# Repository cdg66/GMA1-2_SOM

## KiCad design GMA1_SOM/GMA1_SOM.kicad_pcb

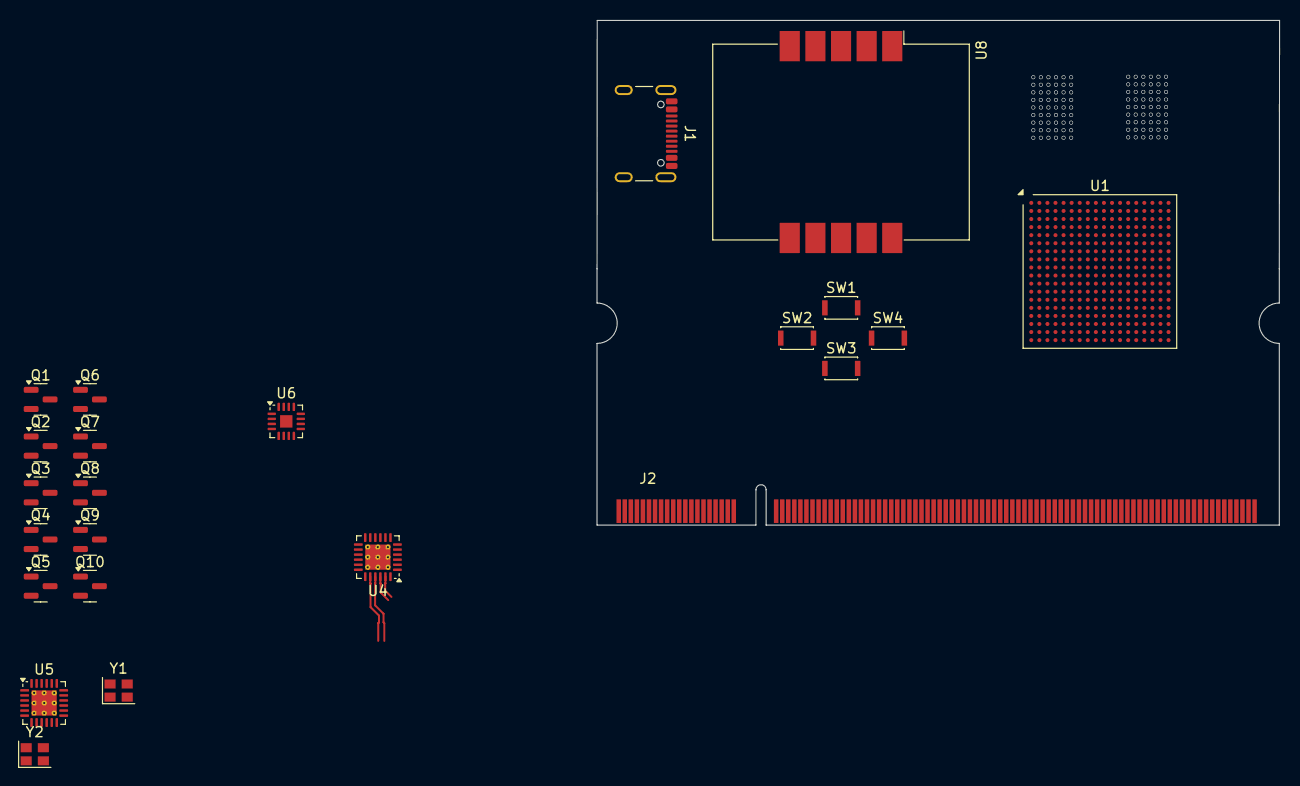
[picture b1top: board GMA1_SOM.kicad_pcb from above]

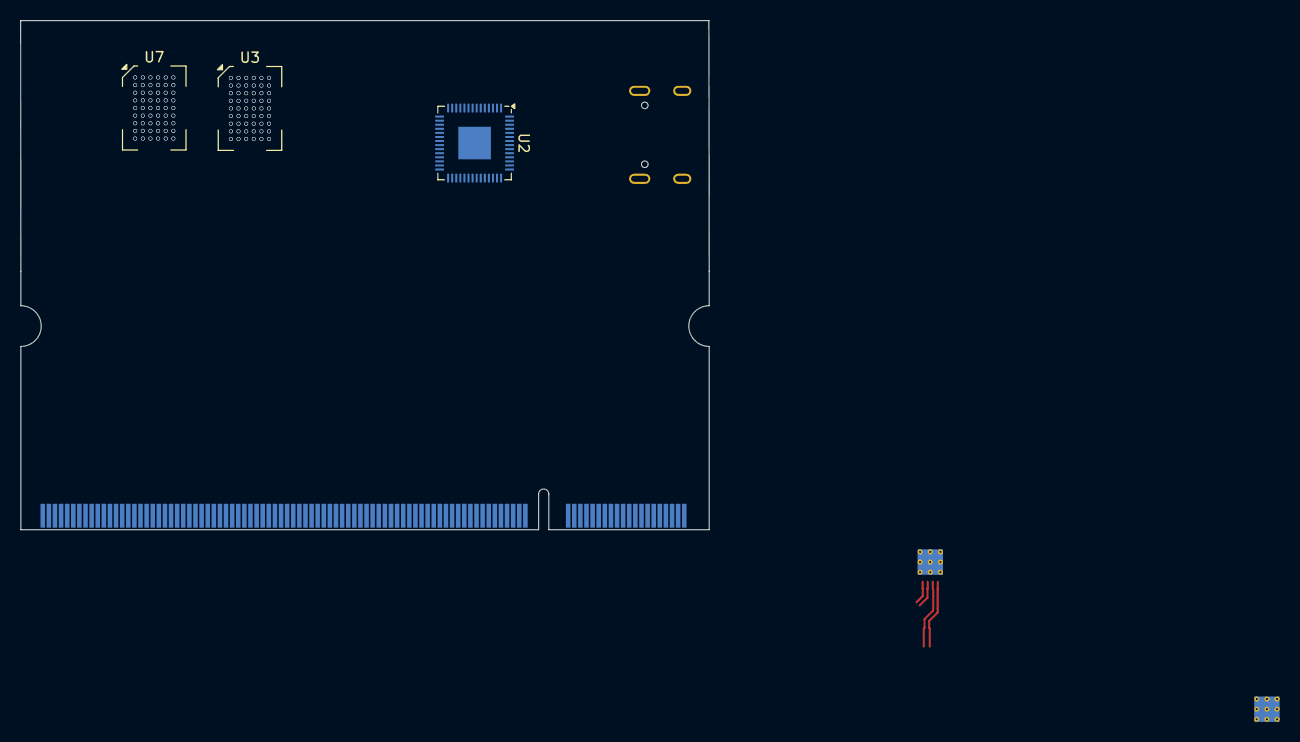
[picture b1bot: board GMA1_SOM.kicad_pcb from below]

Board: 6 copper layers, 67.6 x 50.0 mm, 26 parts (3 on the bottom side), 90 nets.

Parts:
J1: USB4105-GF-A; USB_C_Receptacle_GCT_USB4105-xx-A_16P_TopMnt_Horizontal
J2: SODIMM-200_Split; SODIMM-200_1.8V_Card_edge
Q1, Q2, Q3, Q4, Q5, Q6, Q7, Q8, Q9, Q10: BSS138; SOT-23
SW1, SW2, SW3, SW4: KXT 331 LHS; SW_SPST_CK_KXT3
U1: CCGM1A1; BGA-324_15.0x15.0mm_Layout18x18_P0.8mm_Ball0.45mm_Pad0.4mm_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
U2: RP2040; QFN-56-1EP_7x7mm_P0.4mm_EP3.2x3.2mm
U3, U7: IS66WVC2M16EALL-7010BLI; BGA-54_6x9_6.0x8.0mm
U4, U5: LAN8742A-CZ-TR; VQFN-24-1EP_4x4mm_P0.5mm_EP2.5x2.5mm_ThermalVias
U6: MAX98357B; TQFN-16-1EP_3x3mm_P0.5mm_EP1.23x1.23mm
U8: HDSM-543B; HDSM-541B_HDSM-543B
Y1, Y2: SG-210STF 25.0000ML0; Oscillator_SMD_SeikoEpson_SG210-4Pin_2.5x2.0mm

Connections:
+1V2: U4.6 (VDDCR), U5.6 (VDDCR)
+1V8: U3.D6 (VDD), U3.E1 (VDDQ), U4.9 (VDDIO), U5.9 (VDDIO), U7.D6 (VDD), U7.E1 (VDDQ), Y1.1 (~ST), Y1.4 (Vcc), Y2.1 (~ST), Y2.4 (Vcc)
+3V3A: U4.1 (VDD2A), U4.19 (VDD1A), U5.1 (VDD2A), U5.19 (VDD1A)
/Root/ETHERNET1/RXN: J2.187, U5.22 (RXN)
/Root/ETHERNET1/RXP: J2.189, U5.23 (RXP)
/Root/ETHERNET1/TXN: J2.181, U5.20 (TXN)
/Root/ETHERNET1/TXP: J2.183, U5.21 (TXP)
/Root/ETHERNET/RXN: J2.167, U4.22 (RXN)
/Root/ETHERNET/RXP: J2.169, U4.23 (RXP)
/Root/ETHERNET/TXN: J2.161, U4.20 (TXN)
/Root/ETHERNET/TXP: J2.163, U4.21 (TXP)
/Root/ETHERNET/~INT/REFCLKO: U1.N14 (CLK0/IO_SB_A8), U4.14 (~INT/REFCLKO)
/Root/FPGA/A0: U1.B9 (IO_NB_A0), U3.A3 (A0), U7.A3 (A0)
/Root/FPGA/A1: U1.A9 (IO_NB_B0), U3.A4 (A1), U7.A4 (A1)
/Root/FPGA/A2: U1.D10 (IO_NB_A1), U3.A5 (A2), U7.A5 (A2)
/Root/FPGA/A3: U1.C10 (IO_NB_B1), U3.B3 (A3), U7.B3 (A3)
/Root/FPGA/A4: U1.B11 (IO_NB_A2), U3.B4 (A4), U7.B4 (A4)
/Root/FPGA/A5: U1.A11 (IO_NB_B2), U3.C3 (A5), U7.C3 (A5)
/Root/FPGA/A6: U1.D11 (IO_NB_A3), U3.C4 (A6), U7.C4 (A6)
/Root/FPGA/A7: U1.C11 (IO_NB_B3), U3.D4 (A7), U7.D4 (A7)
/Root/FPGA/A8: U1.B12 (IO_NB_A4), U3.H2 (A8), U7.H2 (A8)
/Root/FPGA/A9: U1.A12 (IO_NB_B4), U3.H3 (A9), U7.H3 (A9)
/Root/FPGA/A10: U1.D12 (IO_NB_A5), U3.H4 (A10), U7.H4 (A10)
/Root/FPGA/A11: U1.C12 (IO_NB_B5), U3.H5 (A11), U7.H5 (A11)
/Root/FPGA/A12: U1.D13 (IO_NB_A6), U3.G3 (A12), U7.G3 (A12)
/Root/FPGA/A13: U1.C13 (IO_NB_B6), U3.G4 (A13), U7.G4 (A13)
/Root/FPGA/A14: U1.B14 (IO_NB_A7), U3.F3 (A14), U7.F3 (A14)
/Root/FPGA/A15: U1.A14 (IO_NB_B7), U3.F4 (A15), U7.F4 (A15)
/Root/FPGA/A16: U1.D14 (IO_NB_A8), U3.E4 (A16), U7.E4 (A16)
/Root/FPGA/A17: U1.C14 (IO_NB_B8), U3.D3 (A17), U7.D3 (A17)
/Root/FPGA/A18: U1.D9 (IO_NA_B8), U3.H1 (A18), U7.H1 (A18)
/Root/FPGA/A19: U1.C9 (IO_NA_A8), U3.G2 (A19), U7.G2 (A19)
/Root/FPGA/A20: U1.B8 (IO_NA_B7), U3.H6 (A20), U7.H6 (A20)
/Root/FPGA/CLK: U1.G16 (IO_EA_A8), U3.J2 (CLK), U7.J2 (CLK)
/Root/FPGA/CRE: U1.J16 (IO_EA_A5), U3.A6 (CRE), U7.A6 (CRE)
/Root/FPGA/DQ0: U1.G15 (IO_EA_B8), U3.B6 (DQ0), U7.B6 (DQ0)
/Root/FPGA/DQ1: U1.A3 (IO_NA_A0), U3.C5 (DQ1), U7.C5 (DQ1)
/Root/FPGA/DQ2: U1.B3 (IO_NA_B0), U3.C6 (DQ2), U7.C6 (DQ2)
/Root/FPGA/DQ3: U1.A4 (IO_NA_A1), U3.D5 (DQ3), U7.D5 (DQ3)
/Root/FPGA/DQ4: U1.B4 (IO_NA_B1), U3.E5 (DQ4), U7.E5 (DQ4)
/Root/FPGA/DQ5: U1.B5 (IO_NA_A2), U3.F5 (DQ5), U7.F5 (DQ5)
/Root/FPGA/DQ6: U1.C5 (IO_NA_B2), U3.F6 (DQ6), U7.F6 (DQ6)
/Root/FPGA/DQ7: U1.C6 (IO_NA_A3), U3.G6 (DQ7), U7.G6 (DQ7)
/Root/FPGA/DQ8: U1.D6 (IO_NA_B3), U3.B1 (DQ8), U7.B1 (DQ8)
/Root/FPGA/DQ9: U1.A6 (IO_NA_A4), U3.C1 (DQ9), U7.C1 (DQ9)
/Root/FPGA/DQ10: U1.B6 (IO_NA_B4), U3.C2 (DQ10), U7.C2 (DQ10)
/Root/FPGA/DQ11: U1.C7 (IO_NA_A5), U3.D2 (DQ11), U7.D2 (DQ11)
/Root/FPGA/DQ12: U1.D7 (IO_NA_B5), U3.E2 (DQ12), U7.E2 (DQ12)
/Root/FPGA/DQ13: U1.C8 (IO_NA_A6), U3.F2 (DQ13), U7.F2 (DQ13)
/Root/FPGA/DQ14: U1.D8 (IO_NA_B6), U3.F1 (DQ14), U7.F1 (DQ14)
/Root/FPGA/DQ15: U1.A8 (IO_NA_A7), U3.G1 (DQ15), U7.G1 (DQ15)
/Root/FPGA/IO_WB_A2: SW4.2, U1.L3 (IO_WB_A2)
/Root/FPGA/IO_WB_A3: SW1.2, U1.L1 (IO_WB_A3)
/Root/FPGA/IO_WB_B2: SW3.2, U1.L4 (IO_WB_B2)
/Root/FPGA/IO_WB_B3: SW2.2, U1.L2 (IO_WB_B3)
/Root/FPGA/WAIT0: U1.J18 (IO_EA_A4), U3.J1 (WAIT)
/Root/FPGA/WAIT1: U1.K15 (IO_EA_B3), U7.J1 (WAIT)
/Root/FPGA/~ADV: U1.G17 (IO_EA_B7), U3.J3 (~ADV), U7.J3 (~ADV)
/Root/FPGA/~CE: U1.H15 (IO_EA_B6), U3.B5 (~CE), U7.B5 (~CE)
/Root/FPGA/~LB: U1.J15 (IO_EA_B5), U3.A1 (~LB), U7.A1 (~LB)
/Root/FPGA/~OE: U1.J17 (IO_EA_B4), U3.A2 (~OE), U7.A2 (~OE)
/Root/FPGA/~UB: U1.H16 (IO_EA_A6), U3.B2 (~UB), U7.B2 (~UB)
/Root/FPGA/~WE: U1.G18 (IO_EA_A7), U3.G5 (~WE), U7.G5 (~WE)
GND: J1.A1 (GND), J1.A12 (GND), J1.B1 (GND), J1.B12 (GND), J2.165, J2.171, J2.177, J2.179, J2.185, J2.191, J2.197, J2.199, Q2.3 (D), Q3.3 (D), SW1.1, SW2.1, SW3.1, SW4.1, U1.A1 (GND), U1.A7 (GND), U1.A10 (GND), U1.A13 (GND), U1.A18 (GND), U1.B16 (GND), U1.C1 (GND), U1.E5 (GND), U1.E7 (GND), U1.E9 (GND), U1.E11 (GND), U1.E13 (GND), U1.E18 (GND), U1.F1 (GND), U1.F6 (GND), U1.F8 (GND), U1.F10 (GND), U1.F12 (GND), U1.F14 (GND), U1.G5 (GND), U1.G7 (GND), U1.G9 (GND), U1.G11 (GND), U1.G13 (GND), U1.H6 (GND), U1.H8 (GND), U1.H10 (GND), U1.H12 (GND), U1.H14 (GND), U1.H18 (GND), U1.J1 (GND), U1.J5 (GND), U1.J7 (GND), U1.J9 (GND), U1.J11 (GND), U1.J13 (GND), U1.K6 (GND), U1.K8 (GND), U1.K10 (GND), U1.K12 (GND), U1.K14 (GND), U1.L5 (GND), U1.L7 (GND), U1.L9 (GND), U1.L11 (GND), U1.L13 (GND), U1.L18 (GND), U1.M1 (GND), U1.M6 (GND), U1.M8 (GND), U1.M10 (GND), U1.M12 (GND), U1.M16 (GND), U1.N7 (GND), U1.N9 (GND), U1.N12 (GND), U1.N17 (GND), U1.P4 (GND), U1.P7 (GND), U1.P9 (GND), U1.R12 (GND), U1.R16 (GND), U1.T4 (GND), U1.T11 (GND), U1.T17 (GND), U1.U14 (GND), U1.U15 (GND), U1.U16 (GND), U1.V1 (GND), U1.V6 (GND), U1.V9 (GND), U1.V14 (GND), U1.V16 (GND), U1.V18 (GND), U3.D1 (VSSQ), U3.E6 (VSS), U4.25 (VSS), U5.25 (VSS), U7.D1 (VSSQ), U7.E6 (VSS), Y1.2 (GND), Y2.2 (GND)
unnamed: J1.A4 (VBUS), J1.A9 (VBUS), J1.B4 (VBUS), J1.B9 (VBUS)
unnamed: Q1.2 (S), U8.1 (G)
unnamed: Q2.2 (S), U8.10 (CC_DIG1)
unnamed: Q3.2 (S), U8.5 (CC_DIG2)
unnamed: Q4.2 (S), U8.2 (DP)
unnamed: Q5.2 (S), U8.3 (A)
unnamed: Q6.2 (S), U8.4 (F)
unnamed: Q7.2 (S), U8.6 (D)
unnamed: Q8.2 (S), U8.7 (E)
unnamed: Q9.2 (S), U8.8 (C)
unnamed: Q10.2 (S), U8.9 (B)
unnamed: U1.N5 (VDD_WA), U1.P3 (VDD_WA), U1.P5 (VDD_WA), U1.T1 (VDD_WA), U1.U3 (VDD_WA)
unnamed: U1.A5 (VDD_NA), U1.B7 (VDD_NA), U1.E6 (VDD_NA), U1.E8 (VDD_NA), U1.F7 (VDD_NA)
unnamed: U1.B10 (VDD_NB), U1.B13 (VDD_NB), U1.E10 (VDD_NB), U1.E12 (VDD_NB), U1.F11 (VDD_NB)
unnamed: U1.G14 (VDD_EA), U1.H17 (VDD_EA), U1.J14 (VDD_EA), U1.L14 (VDD_EA), U1.L17 (VDD_EA)
unnamed: U1.A16 (VDD_EB), U1.B18 (VDD_EB), U1.E14 (VDD_EB), U1.E17 (VDD_EB), U1.F13 (VDD_EB)
unnamed: U1.P6 (VDD_SA), U1.P8 (VDD_SA), U1.P10 (VDD_SA), U1.U6 (VDD_SA), U1.U9 (VDD_SA)
unnamed: U1.N11 (VDD_SB), U1.N13 (VDD_SB), U1.N18 (VDD_SB), U1.R15 (VDD_SB), U1.T18 (VDD_SB)
unnamed: U1.H5 (VDD_WB), U1.J2 (VDD_WB), U1.K5 (VDD_WB), U1.M2 (VDD_WB), U1.M5 (VDD_WB)
unnamed: U1.A2 (VDD_WC), U1.C2 (VDD_WC), U1.D5 (VDD_WC), U1.F2 (VDD_WC), U1.F5 (VDD_WC)
unnamed: U1.F9 (VDD), U1.G6 (VDD), U1.G8 (VDD), U1.G10 (VDD), U1.G12 (VDD), U1.H7 (VDD), U1.H9 (VDD), U1.H11 (VDD), U1.H13 (VDD), U1.J6 (VDD), U1.J8 (VDD), U1.J10 (VDD), U1.J12 (VDD), U1.K7 (VDD), U1.K9 (VDD), U1.K11 (VDD), U1.K13 (VDD), U1.L6 (VDD), U1.L8 (VDD), U1.L10 (VDD), U1.L12 (VDD), U1.M7 (VDD), U1.M9 (VDD), U1.M11 (VDD), U1.M13 (VDD), U1.N6 (VDD), U1.N8 (VDD), U1.N10 (VDD)
unnamed: U1.U12 (VDD_SER), U1.V17 (VDD_SER)
unnamed: U2.23 (DVDD), U2.50 (DVDD)
unnamed: U2.1 (IOVDD), U2.10 (IOVDD), U2.22 (IOVDD), U2.33 (IOVDD), U2.42 (IOVDD), U2.49 (IOVDD)
unnamed: U6.3 (GND), U6.11 (GND), U6.15 (GND)
unnamed: U6.7 (VDD), U6.8 (VDD)

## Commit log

2025-02-24 first draft
2025-02-25 add display and ram
